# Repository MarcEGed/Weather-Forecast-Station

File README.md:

# ESP8266 Based Weather & Forecast Station

An ESP8266-based weather monitoring and prediction system that is extremely cheap to build.

## Features
- Sensor monitoring: temperature, humidity, light, and water/rain levels
- OLED display interface
- WiFi time synchronization and data transmission
- Next-hour prediction (on-edge): neural network on ESP8266 using last 6 hourly readings
- Next-day prediction (online): Python Histogram Gradient Boosting Regressor running on PC, ESP8266 sends current readings via WiFi and receives tomorrow’s forecast

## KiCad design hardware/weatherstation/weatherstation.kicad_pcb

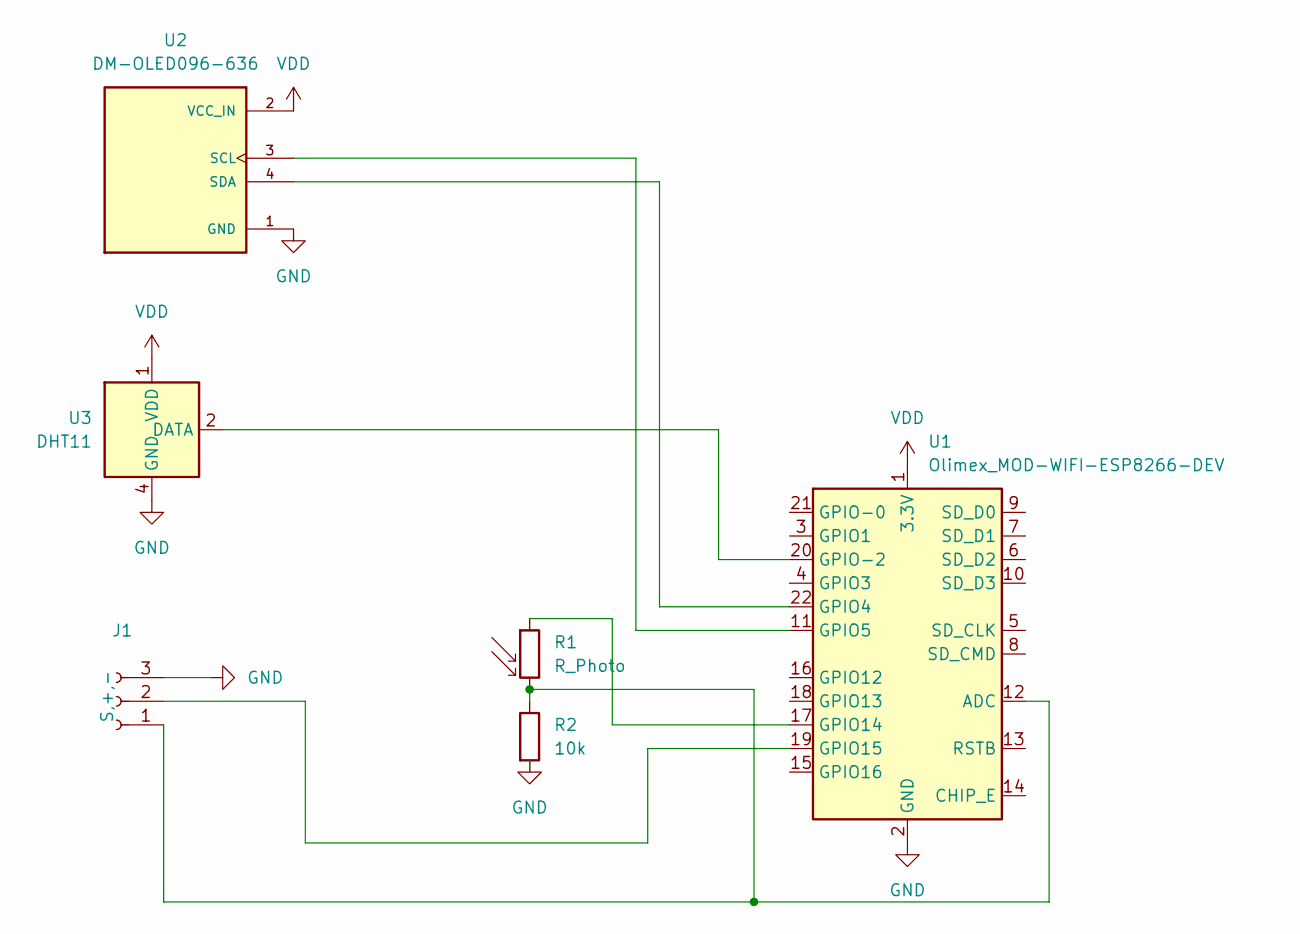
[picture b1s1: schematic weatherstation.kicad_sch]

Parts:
J1: S,+,-; PinSocket_1x03_P1.27mm_Vertical
R1: R_Photo; R_LDR_12x10.8mm_P9.0mm_Vertical
R2: 10k; R_Axial_DIN0204_L3.6mm_D1.6mm_P5.08mm_Horizontal
U1: Olimex_MOD-WIFI-ESP8266-DEV
U2: DM-OLED096-636; Adafruit_SSD1306; PARTREV 2018-09-10
U3: DHT11; Aosong_DHT11_5.5x12.0_P2.54mm

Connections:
GND: J1.3, R2.2, U1.2 (GND), U2.1 (GND), U3.4 (GND)
unnamed: J1.1, R1.2, R2.1, U1.12 (ADC)
unnamed: J1.2, U1.19 (GPIO15)
unnamed: U1.22 (GPIO4), U2.4 (SDA)
unnamed: U1.11 (GPIO5), U2.3 (SCL)
unnamed: R1.1, U1.17 (GPIO14)
unnamed: U1.20 (GPIO-2), U3.2 (DATA)
VDD: U1.1 (3.3V), U2.2 (VCC_IN), U3.1 (VDD)

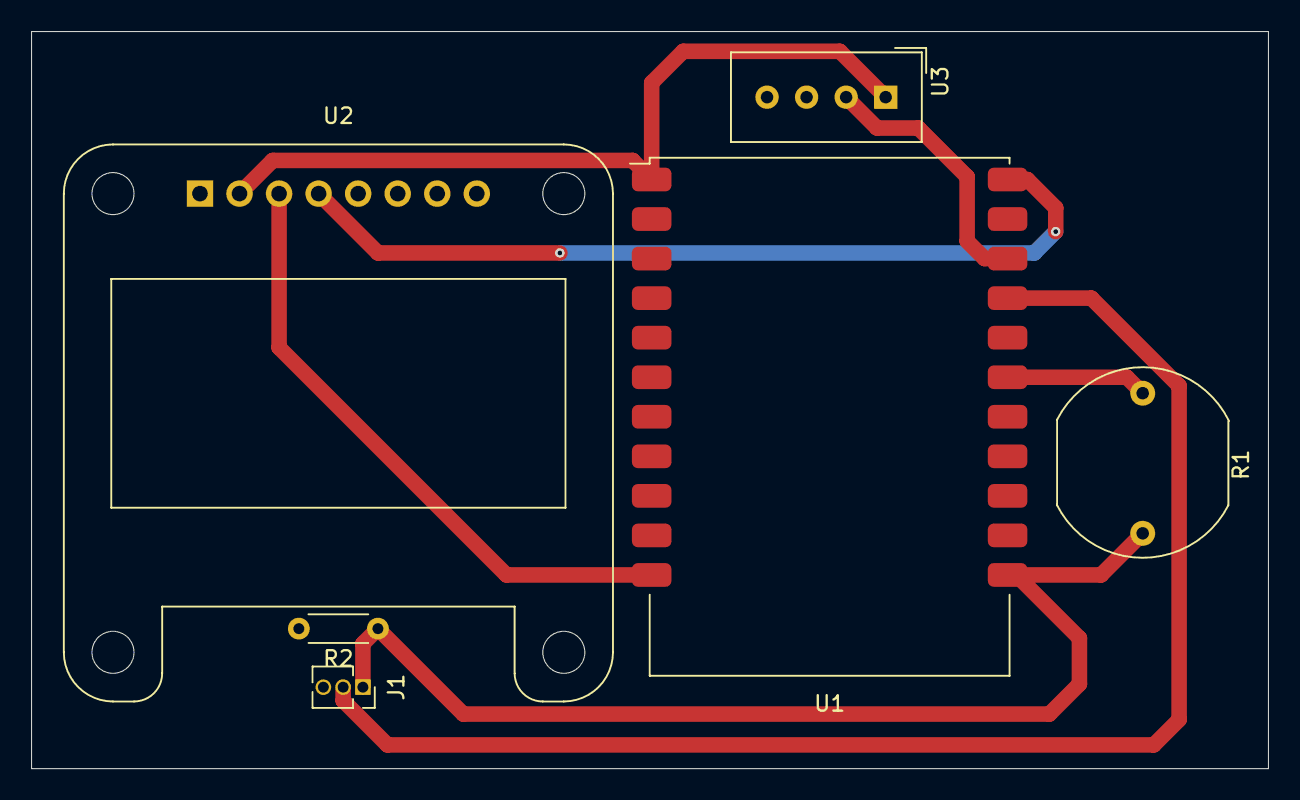
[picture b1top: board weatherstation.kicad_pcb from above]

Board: 2 copper layers, 79.5 x 47.3 mm, 6 parts (0 on the bottom side), 8 nets.

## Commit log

2026-03-10 project upload
2026-03-10 credentials gone + README added
2026-03-11 Added offline mode
